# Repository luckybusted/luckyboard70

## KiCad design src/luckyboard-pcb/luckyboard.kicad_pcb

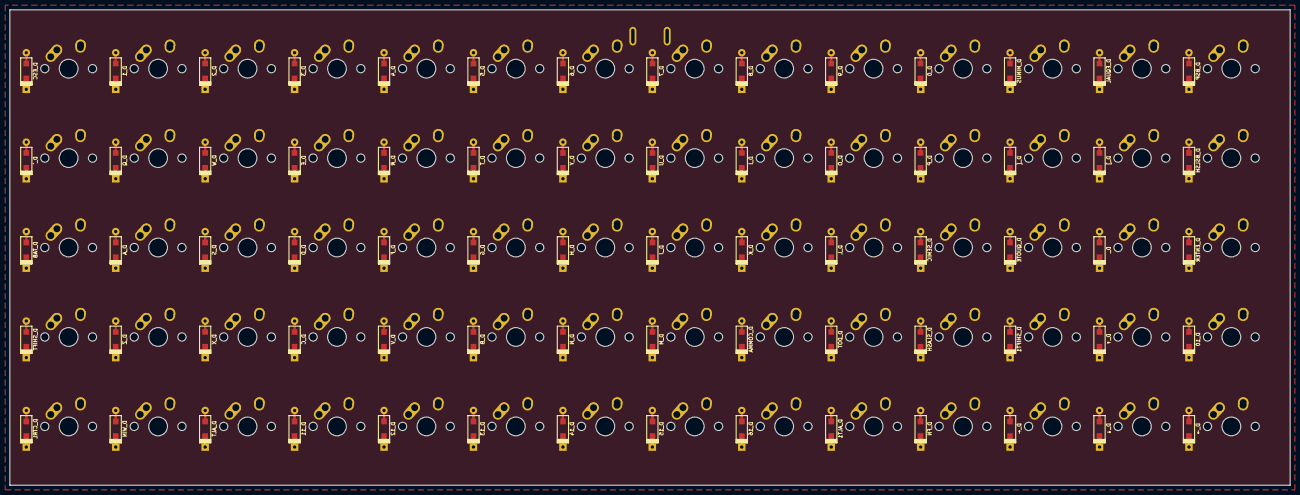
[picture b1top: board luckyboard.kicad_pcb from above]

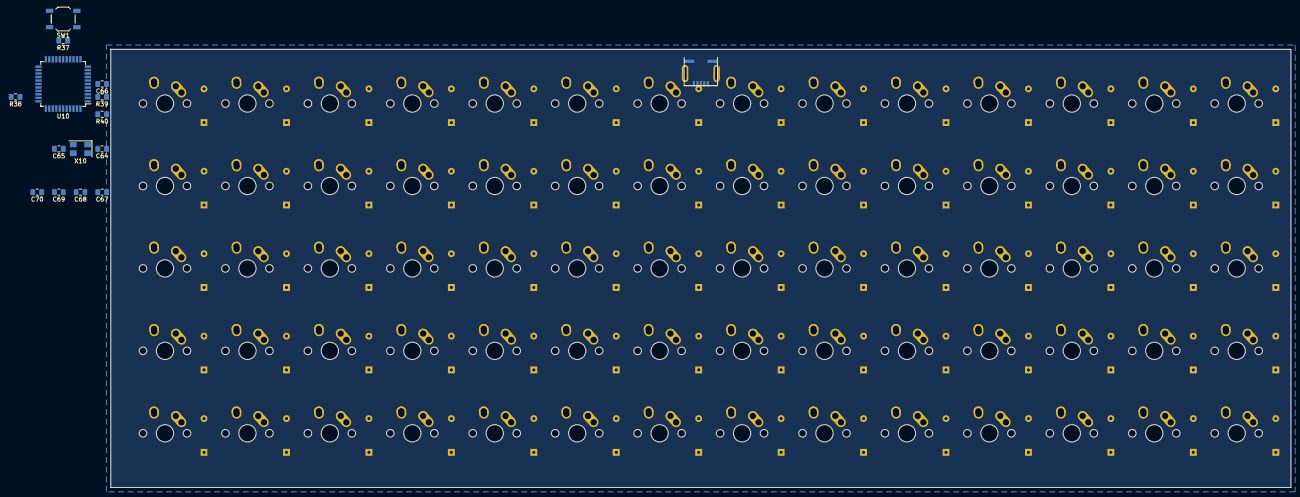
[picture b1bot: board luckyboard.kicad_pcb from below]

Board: 2 copper layers, 272.7 x 101.2 mm, 155 parts (15 on the bottom side), 95 nets, no tracks yet.

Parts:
C64, C65, C66, C67, C68, C69, C70: 22pF; C_0805_2012Metric_Pad1.15x1.40mm_HandSolder
D_, D_0, D_1, D_2, D_3, D_4, D_5, D_6, D_7, D_8, D_9, D_10, D_11, D_12, D_13, D_14, D_15, D_16: D; D_SOD123_axial
D_A: D; D_SOD123_axial
D_ALT, D_ALT1: D; D_SOD123_axial
D_B: D; D_SOD123_axial
D_BSLSH: D; D_SOD123_axial
D_BSP: D; D_SOD123_axial
D_C: D; D_SOD123_axial
D_COMMA: D; D_SOD123_axial
D_CTRL: D; D_SOD123_axial
D_D: D; D_SOD123_axial
D_DOT: D; D_SOD123_axial
D_E: D; D_SOD123_axial
D_ENTER: D; D_SOD123_axial
D_EQUAL: D; D_SOD123_axial
D_ESC: D; D_SOD123_axial
D_F: D; D_SOD123_axial
D_FN: D; D_SOD123_axial
D_G: D; D_SOD123_axial
D_H: D; D_SOD123_axial
D_I: D; D_SOD123_axial
D_J: D; D_SOD123_axial
D_K: D; D_SOD123_axial
D_L: D; D_SOD123_axial
D_M: D; D_SOD123_axial
D_MINUS: D; D_SOD123_axial
D_N: D; D_SOD123_axial
D_O: D; D_SOD123_axial
D_P: D; D_SOD123_axial
D_Q: D; D_SOD123_axial
D_QUOTE: D; D_SOD123_axial
D_R: D; D_SOD123_axial
D_S: D; D_SOD123_axial
D_SEMIC: D; D_SOD123_axial
D_SHIFT, D_SHIFT1: D; D_SOD123_axial
D_SLASH: D; D_SOD123_axial
D_T: D; D_SOD123_axial
D_TAB: D; D_SOD123_axial
D_U: D; D_SOD123_axial
D_V: D; D_SOD123_axial
D_W: D; D_SOD123_axial
D_WIN: D; D_SOD123_axial
D_X: D; D_SOD123_axial
D_Y: D; D_SOD123_axial
D_Z: D; D_SOD123_axial
D_[: D; D_SOD123_axial
D_]: D; D_SOD123_axial
D_`: D; D_SOD123_axial
D_←: D; D_SOD123_axial
D_↑: D; D_SOD123_axial
D_→: D; D_SOD123_axial
D_↓: D; D_SOD123_axial
K_, K_0, K_1, K_2, K_3, K_4, K_5, K_6, K_7, K_8, K_9, K_10, K_11, K_12, K_13, K_14, K_15, K_16: KEYSW; MX-1U-NoLED
K_A: KEYSW; MX-1U-NoLED
K_ALT, K_ALT1: KEYSW; MX-1U-NoLED
K_B: KEYSW; MX-1U-NoLED
K_BSLSH: KEYSW; MX-1U-NoLED
K_BSP: KEYSW; MX-1U-NoLED
K_C: KEYSW; MX-1U-NoLED
K_COMMA: KEYSW; MX-1U-NoLED
K_CTRL: KEYSW; MX-1U-NoLED
K_D: KEYSW; MX-1U-NoLED
K_DOT: KEYSW; MX-1U-NoLED
K_E: KEYSW; MX-1U-NoLED
K_ENTER: KEYSW; MX-1U-NoLED
K_EQUAL: KEYSW; MX-1U-NoLED
K_ESC: KEYSW; MX-1U-NoLED
K_F: KEYSW; MX-1U-NoLED
K_FN: KEYSW; MX-1U-NoLED
K_G: KEYSW; MX-1U-NoLED
K_H: KEYSW; MX-1U-NoLED
K_I: KEYSW; MX-1U-NoLED
K_J: KEYSW; MX-1U-NoLED
K_K: KEYSW; MX-1U-NoLED
K_L: KEYSW; MX-1U-NoLED
K_M: KEYSW; MX-1U-NoLED
K_MINUS: KEYSW; MX-1U-NoLED
K_N: KEYSW; MX-1U-NoLED
K_O: KEYSW; MX-1U-NoLED
K_P: KEYSW; MX-1U-NoLED
K_Q: KEYSW; MX-1U-NoLED
K_QUOTE: KEYSW; MX-1U-NoLED
K_R: KEYSW; MX-1U-NoLED
K_S: KEYSW; MX-1U-NoLED
K_SEMIC: KEYSW; MX-1U-NoLED
K_SHIFT, K_SHIFT1: KEYSW; MX-1U-NoLED
K_SLASH: KEYSW; MX-1U-NoLED
K_T: KEYSW; MX-1U-NoLED
K_TAB: KEYSW; MX-1U-NoLED
K_U: KEYSW; MX-1U-NoLED
K_V: KEYSW; MX-1U-NoLED
K_W: KEYSW; MX-1U-NoLED
K_WIN: KEYSW; MX-1U-NoLED
K_X: KEYSW; MX-1U-NoLED
K_Y: KEYSW; MX-1U-NoLED
K_Z: KEYSW; MX-1U-NoLED
K_[: KEYSW; MX-1U-NoLED
K_]: KEYSW; MX-1U-NoLED
K_`: KEYSW; MX-1U-NoLED
K_←: KEYSW; MX-1U-NoLED
K_↑: KEYSW; MX-1U-NoLED
K_→: KEYSW; MX-1U-NoLED
K_↓: KEYSW; MX-1U-NoLED
R37, R38: 10k; R_0805_2012Metric_Pad1.15x1.40mm_HandSolder
R39, R40: 22u; R_0805_2012Metric_Pad1.15x1.40mm_HandSolder
SW1: SW_PUSH; SW_SPST_TL3342
U10: ATMEGA32U4; TQFP-44_10x10mm_P0.8mm
USB10: USB_mini_micro_B; USB_miniB_hirose_5S8
X10: XTAL_GND; Crystal_SMD_5032-4Pin_5.0x3.2mm

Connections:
/col0: D_CTRL.1, D_ESC.1, D_SHIFT.1, D_TAB.1, D_`.1, U10.32
/col1: D_1.1, D_A.1, D_Q.1, D_WIN.1, D_Z.1, U10.31
/col2: D_2.1, D_ALT.1, D_S.1, D_W.1, D_X.1, U10.12
/col3: D_3.1, D_11.1, D_C.1, D_D.1, D_E.1, U10.30
/col4: D_4.1, D_12.1, D_F.1, D_R.1, D_V.1, U10.29
/col5: D_5.1, D_13.1, D_B.1, D_G.1, D_T.1, U10.28
/col6: D_6.1, D_14.1, D_H.1, D_N.1, D_Y.1, U10.11
/col7: D_7.1, D_15.1, D_J.1, D_M.1, D_U.1, U10.10
/col8: D_8.1, D_16.1, D_COMMA.1, D_I.1, D_K.1, U10.9
/col9: D_9.1, D_ALT1.1, D_DOT.1, D_L.1, D_O.1, U10.8
/col10: D_0.1, D_FN.1, D_P.1, D_SEMIC.1, D_SLASH.1, U10.37
/col11: D_MINUS.1, D_QUOTE.1, D_SHIFT1.1, D_[.1, D_←.1, U10.38
/col12: D_.1, D_EQUAL.1, D_].1, D_↑.1, D_↓.1, U10.39
/col13: D_10.1, D_BSLSH.1, D_BSP.1, D_ENTER.1, D_→.1
GND: C64.2, C65.2, C66.2, C67.2, C68.2, C69.2, C70.2, R38.2, SW1.1, U10.5, U10.15, U10.23, USB10.5, USB10.6, X10.3
unnamed: C64.1, U10.16
unnamed: C65.1, U10.17
unnamed: C66.1, U10.6
unnamed: D_0.2, K_0.2
unnamed: D_1.2, K_1.2
unnamed: D_2.2, K_2.2
unnamed: D_3.2, K_3.2
unnamed: D_4.2, K_4.2
unnamed: D_5.2, K_5.2
unnamed: D_6.2, K_6.2
unnamed: D_7.2, K_7.2
unnamed: D_8.2, K_8.2
unnamed: D_9.2, K_9.2
unnamed: D_10.2, K_10.2
unnamed: D_11.2, K_11.2
unnamed: D_12.2, K_12.2
unnamed: D_13.2, K_13.2
unnamed: D_14.2, K_14.2
unnamed: D_15.2, K_15.2
unnamed: D_16.2, K_16.2
unnamed: D_.2, K_.2
unnamed: D_A.2, K_A.2
unnamed: D_ALT1.2, K_ALT1.2
unnamed: D_ALT.2, K_ALT.2
unnamed: D_B.2, K_B.2
unnamed: D_BSLSH.2, K_BSLSH.2
unnamed: D_BSP.2, K_BSP.2
unnamed: D_C.2, K_C.2
unnamed: D_COMMA.2, K_COMMA.2
unnamed: D_CTRL.2, K_CTRL.2
unnamed: D_D.2, K_D.2
unnamed: D_DOT.2, K_DOT.2
unnamed: D_E.2, K_E.2
unnamed: D_ENTER.2, K_ENTER.2
unnamed: D_EQUAL.2, K_EQUAL.2
unnamed: D_ESC.2, K_ESC.2
unnamed: D_F.2, K_F.2
unnamed: D_FN.2, K_FN.2
unnamed: D_G.2, K_G.2
unnamed: D_H.2, K_H.2
unnamed: D_I.2, K_I.2
unnamed: D_J.2, K_J.2
unnamed: D_K.2, K_K.2
unnamed: D_L.2, K_L.2
unnamed: D_M.2, K_M.2
unnamed: D_MINUS.2, K_MINUS.2
unnamed: D_N.2, K_N.2
unnamed: D_O.2, K_O.2
unnamed: D_P.2, K_P.2
unnamed: D_Q.2, K_Q.2
unnamed: D_QUOTE.2, K_QUOTE.2
unnamed: D_R.2, K_R.2
unnamed: D_S.2, K_S.2
unnamed: D_SEMIC.2, K_SEMIC.2
unnamed: D_SHIFT1.2, K_SHIFT1.2
unnamed: D_SHIFT.2, K_SHIFT.2
unnamed: D_SLASH.2, K_SLASH.2
unnamed: D_T.2, K_T.2
unnamed: D_TAB.2, K_TAB.2
unnamed: D_U.2, K_U.2
unnamed: D_V.2, K_V.2
unnamed: D_W.2, K_W.2
unnamed: D_WIN.2, K_WIN.2
unnamed: D_X.2, K_X.2
unnamed: D_Y.2, K_Y.2
unnamed: D_Z.2, K_Z.2
unnamed: D_[.2, K_[.2
unnamed: D_].2, K_].2
unnamed: D_`.2, K_`.2
unnamed: D_←.2, K_←.2
unnamed: D_↑.2, K_↑.2
unnamed: D_→.2, K_→.2
unnamed: D_↓.2, K_↓.2
unnamed: R37.1, SW1.2, U10.13
unnamed: R38.1, U10.33
unnamed: R39.1, U10.3
unnamed: R40.1, U10.4
unnamed: R39.2, USB10.2
unnamed: R40.2, USB10.3
VCC: C67.1, C68.1, C69.1, C70.1, R37.2, U10.2, U10.14, U10.24, USB10.1

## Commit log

2020-05-19 init
2020-05-19 added the board. working on the scheme
2020-05-24 added scheme and lib
